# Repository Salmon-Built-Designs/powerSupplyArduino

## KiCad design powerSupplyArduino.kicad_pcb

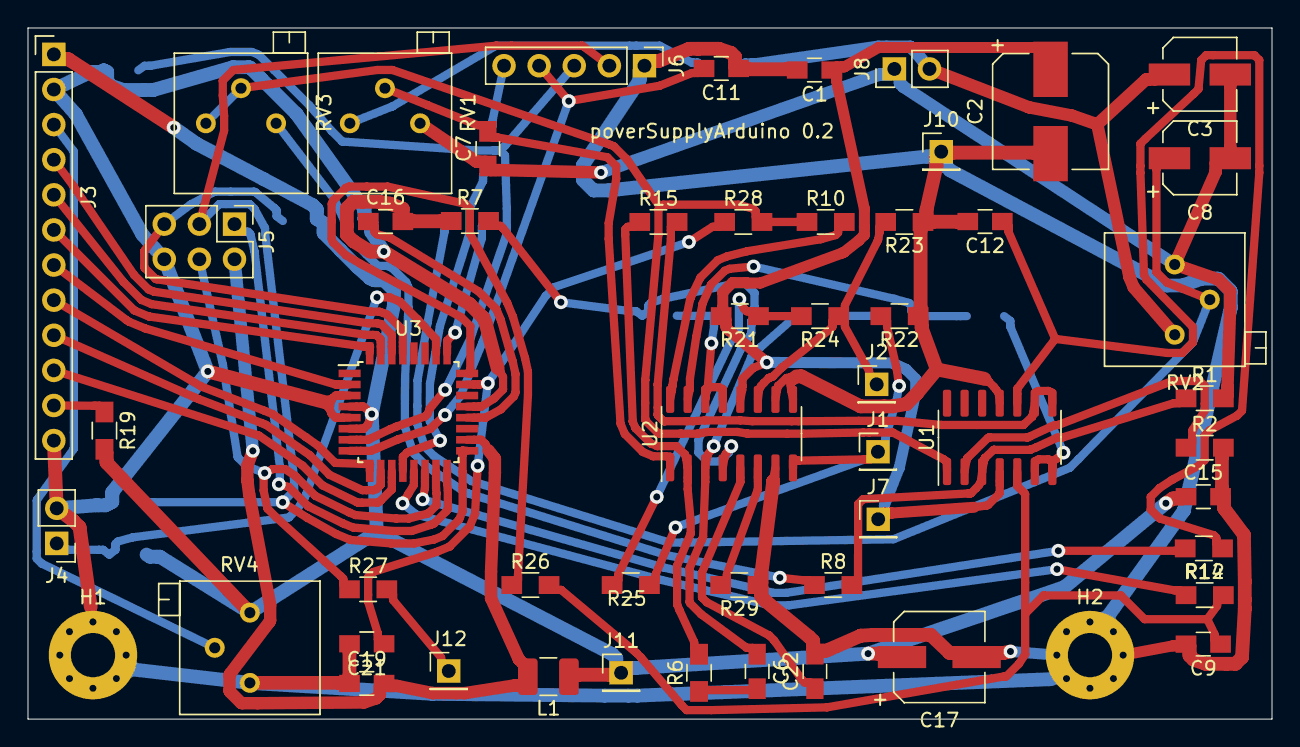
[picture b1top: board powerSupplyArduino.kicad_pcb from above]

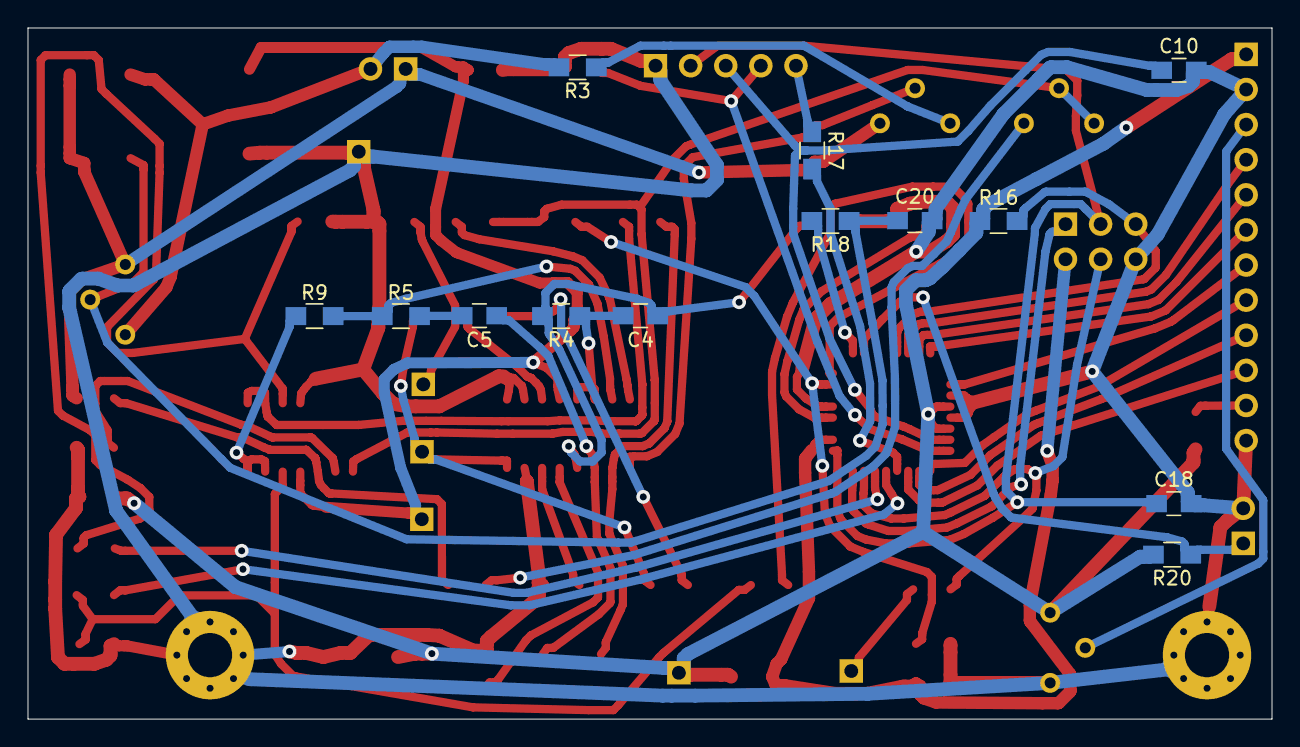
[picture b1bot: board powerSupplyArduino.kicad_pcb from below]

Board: 2 copper layers, 90.0 x 50.0 mm, 68 parts (13 on the bottom side), 55 nets.

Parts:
C1, C15, C19, C20, C21: 100nF; C_0805_HandSoldering
C2: 100uF; CP_Elec_8x6.5
C3: 10uF; CP_Elec_5x5.3
C4: 10uF; C_0805_HandSoldering
C5: 33nF; C_0805_HandSoldering
C6: 150nF; C_0805_HandSoldering
C7, C10, C11, C18: 0.1uF; C_0805_HandSoldering
C8: 22uF; CP_Elec_5x5.3
C9, C12: 4.7uF; C_0805_HandSoldering
C16: 10nF; C_0805_HandSoldering
C17: 100uF; CP_Elec_6.3x5.3
C22: 1nF; C_0805_HandSoldering
H1, H2: MountingHole_3.2mm_M3_Pad_Via
J1: Q3b; Pin_Header_Straight_1x01_Pitch2.54mm
J2: Q4b; Pin_Header_Straight_1x01_Pitch2.54mm
J3: Display; Pin_Header_Straight_1x12_Pitch2.54mm
J4: Termo_sens; Pin_Header_Straight_1x02_Pitch2.54mm
J5: ISP; Pin_Header_Straight_2x03_Pitch2.54mm
J6: Encoder; Pin_Header_Straight_1x05_Pitch2.54mm
J7: +15v; Pin_Header_Straight_1x01_Pitch2.54mm
J8: Supply; Pin_Header_Straight_1x02_Pitch2.54mm
J10: GND; Pin_Header_Straight_1x01_Pitch2.54mm
J11: +5v; Pin_Header_Straight_1x01_Pitch2.54mm
J12: Fun ctrl; Pin_Header_Straight_1x01_Pitch2.54mm
L1: 100uH; L_1210_3225Metric_Pad1.42x2.65mm_HandSolder
R1, R2, R8, R9, R15, R16, R17, R18, R22, R23, R26, R27, R28: 1K; R_0805_HandSoldering
R3: 330; R_0805_HandSoldering
R4: 56K; R_0805_HandSoldering
R5, R6, R10, R20: 100K; R_0805_HandSoldering
R7: 1.8K; R_0805_HandSoldering
R12, R14: 47K; R_0805_HandSoldering
R19: 100; R_0805_HandSoldering
R21: 10; R_0805_HandSoldering
R24, R25: 2K7; R_0805_HandSoldering
R29: 18K; R_0805_HandSoldering
RV1, RV2, RV4: 10K; Potentiometer_Trimmer_Bourns_3299P
RV3: 1K; Potentiometer_Trimmer_Bourns_3299P
U1: LM324; SOIC-14_3.9x8.7mm_P1.27mm
U2: TL494; SOIC-16_3.9x9.9mm_P1.27mm
U3: ATmega8A-AU; TQFP-32_7x7mm_P0.8mm

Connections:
+5V: C15.1, C17.1, J3.1, J11.1, L1.1, R16.1, R19.2, R20.2, RV4.1, U3.4, U3.6
+15V: C1.1, C2.1, J7.1, R21.2, U1.4, U2.12
/A: J3.11, R19.1
/D4: J3.7, U3.2
/D5: J3.8, U3.9
/D6: J3.9, U3.10
/D7: J3.10, U3.11
/E: J3.6, U3.32
/RS: J3.4, U3.30
/RW: J3.5, U3.31
/Vo: J3.3, RV4.2
Encoder_A: C10.1, J6.3, U3.7
Encoder_B: C11.2, J6.4, U3.8
Encoder_S: C18.1, J5.3, J6.2, U3.17
FAN_CNTR: J12.1, R27.2
GND: C1.2, C2.2, C9.2, C10.2, C11.1, C12.2, C15.2, C16.2, C17.2, C18.2, C19.1, C20.2, C21.2, C22.2, H1.1, H2.1, J3.2, J3.12, J4.2, J5.6, J6.1, J10.1, R2.2, R7.1, R22.1, R23.1, R29.1, RV4.3, U1.11, U2.7, U2.9, U2.10, U3.3, U3.5, U3.21
ISP_RESET: J5.5, R16.2, U3.29
ISP_VCC: C19.2, J5.2, L1.2, U3.18
LED_CUR: J6.5, R17.1
MISO: J5.1, U3.16
MOSI: J5.4, R27.1, U3.15
unnamed: C4.1, R4.2, R7.2, U2.4
unnamed: C4.2, R4.1, U2.13, U2.14
unnamed: C5.1, C6.1, U2.3
unnamed: C5.2, R5.2
unnamed: C6.2, R6.1
unnamed: C7.2, RV1.2, U2.1
unnamed: C9.1, R12.2, R26.2, U1.5
unnamed: C12.1, R14.1, U1.10
unnamed: C16.1, U3.20
unnamed: C8.1, C20.1, R18.1, RV2.2
unnamed: C21.1, R28.1, U3.23
unnamed: C22.1, U2.5
unnamed: R1.1, R8.2, U1.3
unnamed: R2.1, U1.2
unnamed: R3.1, RV1.3
unnamed: R5.1, R9.2, U2.15
unnamed: R8.1, RV3.1
unnamed: R9.1, U1.6, U1.7
unnamed: R10.1, R28.2, RV3.2, RV3.3, U1.1
unnamed: R10.2, U2.16
unnamed: R12.1, U3.13
unnamed: R14.2, U3.14
unnamed: R6.2, R15.1, U2.2
unnamed: R15.2, U1.8, U1.9
unnamed: R17.2, U3.12
unnamed: R18.2, U3.25
unnamed: R21.1, R24.2, R25.2
unnamed: R26.1, U3.24
unnamed: R29.2, U2.6
Q3Base: J1.1, R22.2, R25.1, U2.8
Q4Base: J2.1, R23.2, R24.1, U2.11
Supply+: C3.1, J8.2, R3.2, RV2.1
Supply-: C3.2, C7.1, C8.2, J8.1, R1.2, RV1.1, RV2.3
TERMO_SENS: J4.1, R20.1, U3.26

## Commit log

2019-10-28 first
2019-10-28 encoder
2019-10-28 wo input lines
2019-10-29 add q3 q4 base lines
2019-10-30 fix led error, recalc curent implefier loop back resistors
2019-10-30 fix design
2019-10-30 add termo sense, fix errors
2019-10-31 add rc for lm494
2019-10-31 created pcb
2019-11-01 first try to routing
2019-11-01 change position
2019-11-01 v6 shema added
2019-11-03 charnge positions. start autorouting
2019-11-04 charnge positions. start autorouting again
2019-11-05 charnge positions. start autorouting again 2
2019-11-05 width chnged to .6 mm
2019-11-05 routing complite
2019-11-05 add zones
2019-11-08 changes for pcbway
2019-11-08 new positions
2019-11-08 gerber
2019-12-23 v .2 fixed intersect of mount pad and some track
2019-12-23 change rv2 value to 10k, add bom
2019-12-23 aref c changed, add xsl bom
2019-12-25 add bom
2019-12-29 git ignore
2019-12-29 make pwm started
2019-12-29 timer1 enable as pwm
2019-12-29 refresh display onli if it is needed
2019-12-29 settings of timer1 was comming back
2019-12-30 add adc logic
2020-01-11 firmware updated
2020-01-19 firmware first release
2020-01-19 added power check
2020-01-25 add charge mode
2020-01-25 change copyValToStr
